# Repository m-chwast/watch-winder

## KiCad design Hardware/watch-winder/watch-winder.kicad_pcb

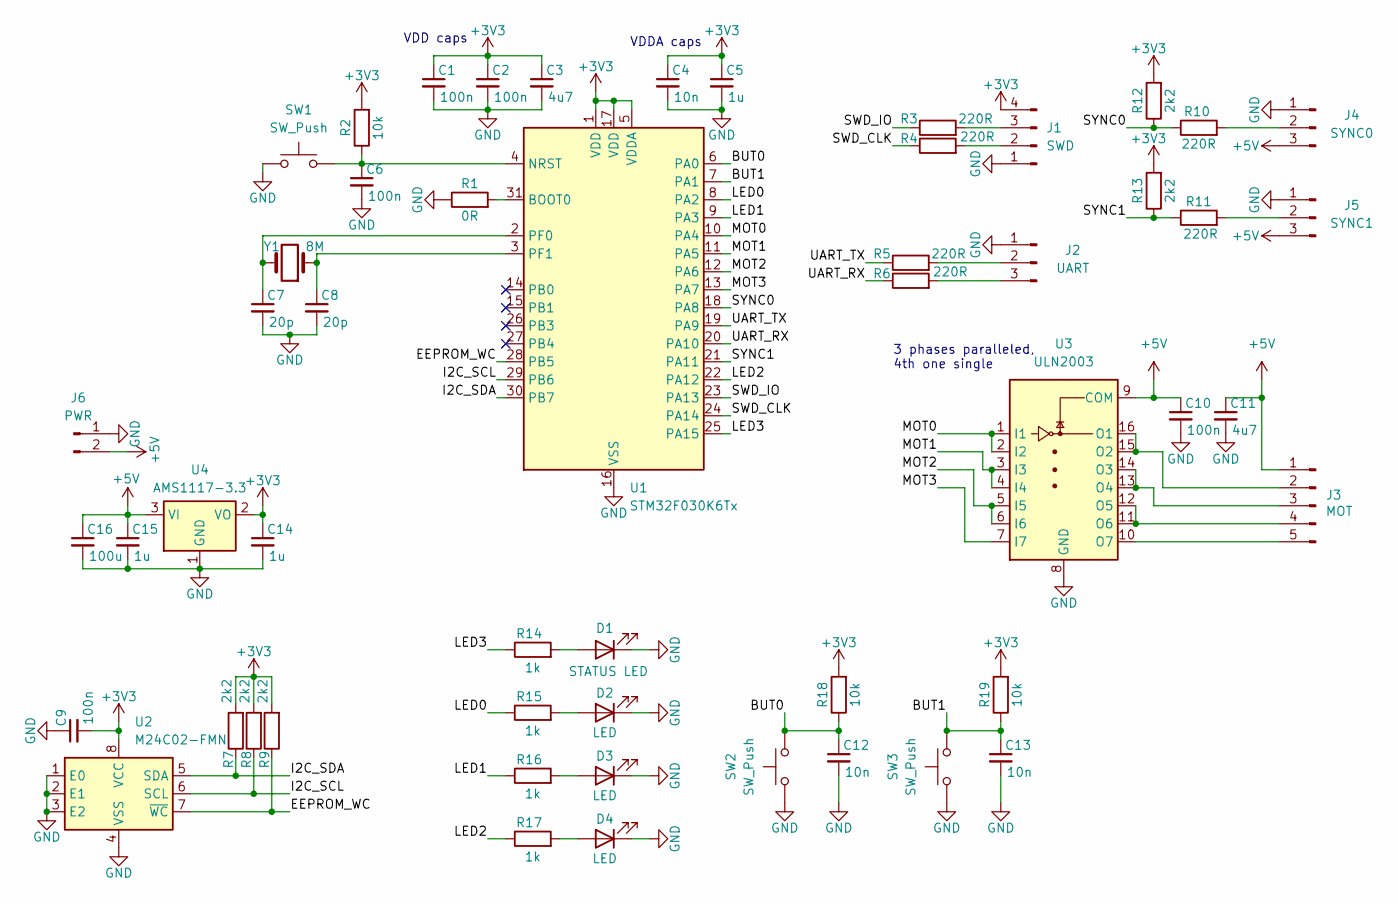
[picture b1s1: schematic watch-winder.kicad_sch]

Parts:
C1, C2, C6, C9, C10: 100n; C_0805_2012Metric_Pad1.18x1.45mm_HandSolder
C3, C11: 4u7; C_0805_2012Metric_Pad1.18x1.45mm_HandSolder
C4, C12, C13: 10n; C_0805_2012Metric_Pad1.18x1.45mm_HandSolder
C5, C14, C15: 1u; C_0805_2012Metric_Pad1.18x1.45mm_HandSolder
C7, C8: 20p; C_0805_2012Metric_Pad1.18x1.45mm_HandSolder
C16: 100u; C_Radial_D5.0mm_H5.0mm_P2.00mm
D1: STATUS LED; LED_0805_2012Metric_Pad1.15x1.40mm_HandSolder
D2, D3, D4: LED; LED_D5.0mm
J1: SWD; PinHeader_1x04_P2.54mm_Horizontal
J2: UART; PinHeader_1x03_P2.54mm_Vertical
J3: MOT; PinHeader_1x05_P2.54mm_Vertical
J4: SYNC0; PinHeader_1x03_P2.54mm_Vertical
J5: SYNC1; PinHeader_1x03_P2.54mm_Vertical
J6: PWR; PinHeader_1x02_P2.54mm_Horizontal
R1: 0R; R_0805_2012Metric_Pad1.20x1.40mm_HandSolder
R2, R18, R19: 10k; R_0805_2012Metric_Pad1.20x1.40mm_HandSolder
R3, R4, R5, R6, R10, R11: 220R; R_0805_2012Metric_Pad1.20x1.40mm_HandSolder
R7, R8, R9, R12, R13: 2k2; R_0805_2012Metric_Pad1.20x1.40mm_HandSolder
R14, R15, R16, R17: 1k; R_0805_2012Metric_Pad1.20x1.40mm_HandSolder
SW1, SW2, SW3: SW_Push; SW_PUSH_6mm
U1: STM32F030K6Tx; LQFP-32_7x7mm_P0.8mm
U2: M24C02-FMN; SOIC-8_3.9x4.9mm_P1.27mm
U3: ULN2003; DIP-16_W7.62mm
U4: AMS1117-3.3; SOT-223-3_TabPin2
Y1: 8M; Crystal_HC49-U_Vertical

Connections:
+3V3: C1.1, C2.1, C3.1, C4.1, C5.1, C9.2, C14.1, J1.4, R2.2, R7.2, R8.2, R9.2, R12.2, R13.2, R18.2, R19.2, U1.1 (VDD), U1.5 (VDDA), U1.17 (VDD), U2.8 (VCC), U4.2 (VO)
+5V: C10.1, C11.1, C15.1, C16.1, J3.1, J4.3, J5.3, J6.2, U3.9 (COM), U4.3 (VI)
/BUT0: C12.1, R18.1, SW2.2, U1.6 (PA0)
/BUT1: C13.1, R19.1, SW3.2, U1.7 (PA1)
/EEPROM_WC: R9.1, U1.28 (PB5), U2.7 (~WC)
/I2C_SCL: R8.1, U1.29 (PB6), U2.6 (SCL)
/I2C_SDA: R7.1, U1.30 (PB7), U2.5 (SDA)
/LED0: R15.1, U1.8 (PA2)
/LED1: R16.1, U1.9 (PA3)
/LED2: R17.1, U1.22 (PA12)
/LED3: R14.1, U1.25 (PA15)
/MOT0: U1.10 (PA4), U3.1 (I1), U3.2 (I2)
/MOT1: U1.11 (PA5), U3.3 (I3), U3.4 (I4)
/MOT2: U1.12 (PA6), U3.5 (I5), U3.6 (I6)
/MOT3: U1.13 (PA7), U3.7 (I7)
/SWD_CLK: R4.1, U1.24 (PA14)
/SWD_IO: R3.1, U1.23 (PA13)
/SYNC0: R10.1, R12.1, U1.18 (PA8)
/SYNC1: R11.1, R13.1, U1.21 (PA11)
/UART_RX: R6.1, U1.20 (PA10)
/UART_TX: R5.1, U1.19 (PA9)
GND: C1.2, C2.2, C3.2, C4.2, C5.2, C6.2, C7.2, C8.2, C9.1, C10.2, C11.2, C12.2, C13.2, C14.2, C15.2, C16.2, D1.1 (K), D2.1 (K), D3.1 (K), D4.1 (K), J1.1, J2.1, J4.1, J5.1, J6.1, R1.1, SW1.1, SW2.1, SW3.1, U1.16 (VSS), U1.32 (VSS), U2.1 (E0), U2.2 (E1), U2.3 (E2), U2.4 (VSS), U3.8 (GND), U4.1 (GND)
unnamed: D1.2 (A), R14.2
unnamed: D2.2 (A), R15.2
unnamed: D3.2 (A), R16.2
unnamed: D4.2 (A), R17.2
unnamed: J1.2, R4.2
unnamed: J1.3, R3.2
unnamed: J2.2, R5.2
unnamed: J2.3, R6.2
unnamed: J3.2, U3.15 (O2), U3.16 (O1)
unnamed: J3.3, U3.13 (O4), U3.14 (O3)
unnamed: J3.4, U3.11 (O6), U3.12 (O5)
unnamed: J3.5, U3.10 (O7)
unnamed: J4.2, R10.2
unnamed: J5.2, R11.2
unnamed: R1.2, U1.31 (BOOT0)
unnamed: C6.1, R2.1, SW1.2, U1.4 (NRST)
unnamed: C7.1, U1.2 (PF0), Y1.2
unnamed: C8.1, U1.3 (PF1), Y1.1

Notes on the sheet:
VDDA caps
3 phases paralleled, 4th one single
VDD caps

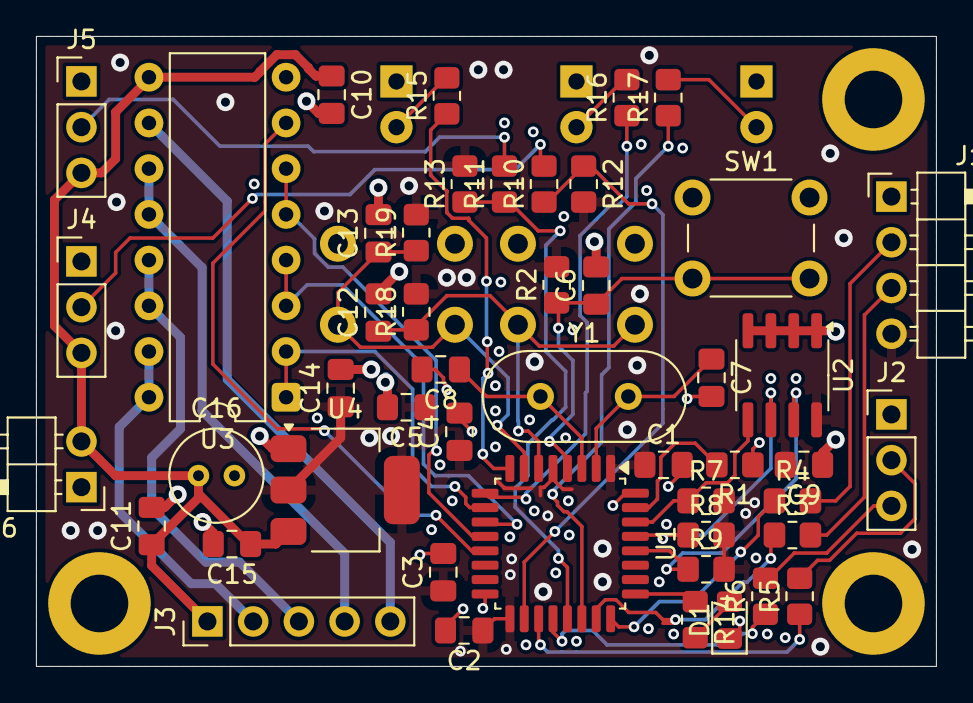
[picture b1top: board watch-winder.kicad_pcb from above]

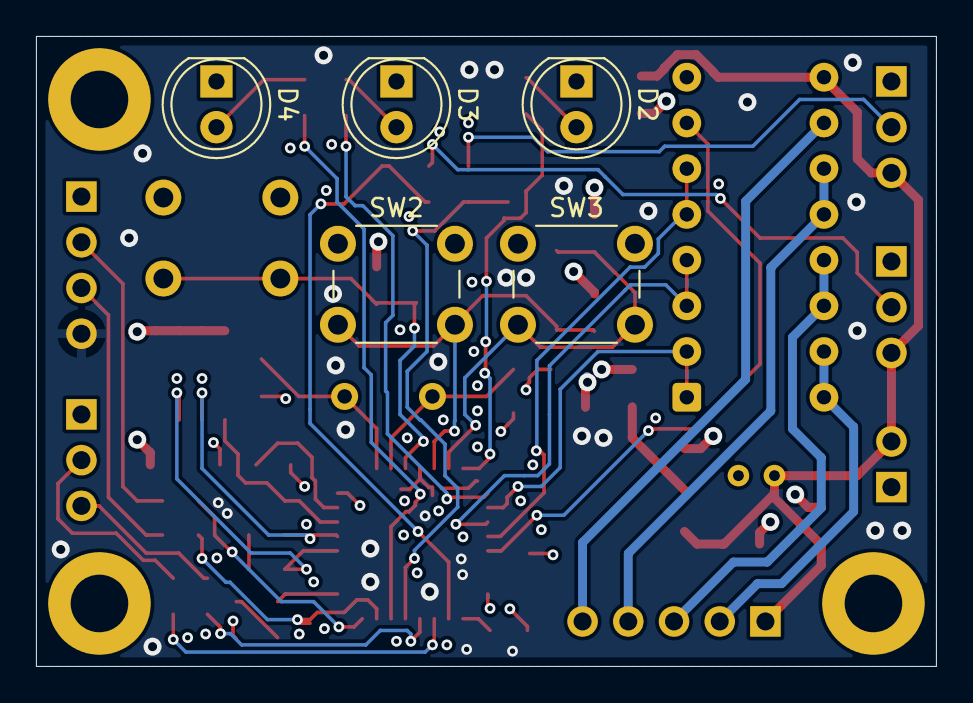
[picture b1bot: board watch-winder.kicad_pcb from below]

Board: 4 copper layers, 50.0 x 35.0 mm, 53 parts (5 on the bottom side), 40 nets.

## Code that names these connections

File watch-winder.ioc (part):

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Mcu.Name=STM32F030F4Px
Mcu.Package=TSSOP20
Mcu.UserName=STM32F030F4Px
PA0.GPIOParameters=GPIO_Label
PA0.GPIO_Label=MOTOR_OUT1
PA0.Signal=GPIO_Output
PA1.GPIOParameters=GPIO_Label
PA1.GPIO_Label=MOTOR_OUT2
PA1.Signal=GPIO_Output
PA10.Mode=Asynchronous
PA10.Signal=USART1_RX
PA13.Mode=Serial_Wire
PA13.Signal=SYS_SWDIO
PA14.Mode=Serial_Wire
PA14.Signal=SYS_SWCLK
PA2.GPIOParameters=GPIO_Label
PA2.GPIO_Label=MOTOR_OUT3
PA2.Signal=GPIO_Output
PA3.GPIOParameters=GPIO_Label
PA3.GPIO_Label=MOTOR_OUT4
PA3.Signal=GPIO_Output
PA4.GPIOParameters=GPIO_Label
PA4.GPIO_Label=LED0
PA4.Signal=GPIO_Output
PA5.GPIOParameters=GPIO_Label
PA5.GPIO_Label=LED1
PA5.Signal=GPIO_Output
PA6.GPIOParameters=GPIO_PuPd,GPIO_Label,GPIO_ModeDefaultEXTI
PA6.GPIO_Label=BUTTON0
PA6.GPIO_ModeDefaultEXTI=GPIO_MODE_IT_FALLING
PA6.GPIO_PuPd=GPIO_PULLUP
PA6.Signal=GPXTI6
PA7.GPIOParameters=GPIO_PuPd,GPIO_Label,GPIO_ModeDefaultEXTI
PA7.GPIO_Label=BUTTON1
PA7.GPIO_ModeDefaultEXTI=GPIO_MODE_IT_FALLING
PA7.GPIO_PuPd=GPIO_PULLUP
PA7.Signal=GPXTI7
PA9.Mode=Asynchronous
PA9.Signal=USART1_TX
PF0-OSC_IN.Mode=HSE-External-Oscillator
PF0-OSC_IN.Signal=RCC_OSC_IN
PF1-OSC_OUT.Mode=HSE-External-Oscillator
PF1-OSC_OUT.Signal=RCC_OSC_OUT
RCC.SYSCLKFreq_VALUE=48000000
RCC.SYSCLKSource=RCC_SYSCLKSOURCE_PLLCLK
board=custom

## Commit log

2023-10-17 add gitignore
2023-10-17 add stm32cubeide project
    initial setup for STM32F030 Demo Board:
    - HSE 8 MHz with PLL x6 (48 MHz clock)
    - Serial Wire Debug
    - PA4 as output for onboard LED
2023-10-17 setup uart1
2023-10-17 add basic logging function and console module
2023-10-17 add log numeric function
2023-10-17 setup gpio pins for stepper motor
2023-10-17 add program module called from main loop
2023-10-17 add Program folder to include paths
2023-10-17 move non-generated files to Program folder
2023-10-17 add motor module
2023-10-17 add Motor_Step function prototype
2023-10-17 fix motor_out3 pin setup
2023-10-17 implement simple single dir wave drive
2023-10-17 set and reset pins in one function
2023-10-17 implement dir selection, use full-drive
2023-10-17 add test variable dir movement
2023-10-18 implement drive mode selection
2023-10-18 implement wave drive
2023-10-18 implement half step drive
2023-10-18 move defines to header, add steps per revolution
2023-10-18 setup tim14 as 1us-tick timer
2023-10-18 add motor struct and setMovement function for setting steps and dir
2023-10-18 add logError function to console
2023-10-18 add console messages while setting movement
2023-10-18 set test movement
2023-10-18 enable tim14 interrupt
2023-10-18 add timers module
2023-10-18 start timer in movement set
2023-10-18 move motorPinsWrite under the step function
2023-10-18 implement motor irq handler
2023-10-18 implement motor speed
2023-10-18 move motor defines to source file
2023-10-18 save ramp steps and init speed
2023-10-18 implement start ramp
2023-10-18 implement finish ramp
2023-10-18 reduce the ramps slightly
2023-10-18 set -og optimization
2023-10-18 make whole motor struct volatile
2023-10-18 configure PA6 and PA7 as falling edge exti inputs for buttons
2023-10-18 add buttons module with exti callback
2023-10-18 add button manage function
2023-10-18 add pin and gpio to button, add state switch in button manage
2023-10-18 implement released state
2023-10-18 add print status function
2023-10-18 implement debouncing
2023-10-18 implement pressed state
2023-10-18 implement late release callback
2023-10-19 add function for setting button callbacks
2023-10-19 add modes module
2023-10-19 implement mode set next
2023-10-19 replace set active/inactive edit mode functions with toggle functions
2023-10-19 set button callbacks
2023-10-19 log enabling mode editing
2023-10-19 add getters for modes
2023-10-19 add leds module
2023-10-19 set pa5 as output, rename pa4-5 to led0-1
2023-10-19 add basic typedefs for standard leds
    also change code formatter slightly
2023-10-19 create ledCounter type and two instances
2023-10-19 add led interface to header, call beginInit
2023-10-19 add state switch in ledManage
2023-10-19 add function for writing to led
2023-10-19 implement init start/finsh states, add cnt var to led struct
2023-10-19 implement led initialization
2023-10-19 remove init finish state
2023-10-19 print led init status
2023-10-19 call led counter manager from idle state
2023-10-19 add led counter state
2023-10-19 add callbacks for led counter
2023-10-19 set callbacks for led counters
2023-10-19 implement idle counter state
2023-10-19 implement led counter blinking
2023-10-19 adjust blinking periods
2023-10-19 provide incremented modes value to led counters
2023-10-19 add longPressing button callback
2023-10-19 call onLongPressed button callback
2023-10-19 toggle edit active on long pressed
2023-10-19 add program manage call to program loop
2023-10-19 configure rtc with calendar and alarm
2023-10-19 add rtc module
2023-10-19 implement setting the next alarm
2023-10-19 implement cyclic alarms
2023-10-19 handle setting new alarm in main loop instead of in irq
2023-10-19 set rotation request via alarm callback
2023-10-19 run motor on rtc alarm
2023-10-19 turn motor power off after movement
2023-10-19 use macro for rev to degrees conversion
2023-10-19 use callback for getting rtc period
2023-10-19 create rtc struct
2023-10-19 add modes enums
2023-10-19 add getter for revs per cycle
2023-10-19 implement getters for turns per cycle and cycle time
2023-10-19 set speed with revs per hour
2023-10-19 print next alarm time on console
2023-10-19 use getter to get timing mode
2023-10-19 replace program manage with watch winder module
2023-10-19 implement idle watch winder state
2023-10-19 implement 4 modes init
2023-10-19 implement rotation state
2023-10-19 add rotation start/finish logs
2023-10-19 use tmp value to change modes
2023-10-19 refresh watch winder on mode change
2023-10-19 fix mode signalling
2023-10-19 fix main mode saving
2023-10-19 add stop states to watch winder
2023-10-19 make motor step static
2023-10-20 implement motor stop request
2023-10-20 implement infinite motor movement
2023-10-20 add constant rotation state
2023-10-20 start motor in constatnt rotation
2023-10-20 refresh watch winder in program init
2023-10-20 implement speed for constant modes
2023-10-20 don't set alarm if period is full day
2023-10-20 fix mode isConstant function
2023-10-20 deactivate alarm if full day period was requested
2023-10-20 reset remaining turns after they've been read
2024-09-16 fix over 24h hour bug
2025-03-29 add empty project
2025-03-29 add stm32 uc
2025-03-29 add decoupling caps
2025-03-29 add reset circuit, fix vdd
2025-03-29 add swd interface
2025-03-29 add hse
2025-03-29 add uart
2025-03-29 add eeprom
2025-03-29 add motor driver
2025-03-29 add motor bus
2025-03-29 add sync ios
2025-03-29 add button/led connectors
2025-03-30 add leds and buttons
2025-03-30 add power section
2025-03-30 update components
2025-03-30 add pcb cutout, set 4 layer stackup
2025-03-30 add gnd planes
2025-03-30 start button/led placement
2025-03-30 fix gnd, more components
2025-03-30 better placement
2025-03-30 more or less final placement
2025-03-30 add no-connect
2025-03-30 lower board size, add mounting holes
2025-03-30 add third mounting hole
2025-03-30 add constraints
2025-03-30 routing
2025-04-02 remove drc errors
2025-04-02 add ground vias near signal vias
2025-04-02 add power vias
